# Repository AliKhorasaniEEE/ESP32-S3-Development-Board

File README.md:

# ESP32-S3 Development Board

A custom ESP32-S3-WROOM-1 development board designed in KiCad.

## Overview

This project is a two-layer ESP32-S3 development board featuring USB Type-C connectivity, USB-to-UART programming, onboard 3.3 V regulation, and access to all ESP32-S3 GPIO pins.

The board was designed as a learning project to gain practical experience in professional PCB design using KiCad.

---

## Features

- ESP32-S3-WROOM-1 module
- USB Type-C connector
- CP2102N USB-to-UART bridge
- AMS1117-3.3 V voltage regulator
- Reset and Boot buttons
- All 40 ESP32-S3 pins exposed
- Two-layer PCB
- Ground plane
- Decoupling capacitors placed according to the reference design

---

## Main Components

| Component | Part Number |
|-----------|-------------|
| MCU | ESP32-S3-WROOM-1 |
| USB-UART | CP2102N |
| Voltage Regulator | AMS1117-3.3 |
| USB Connector | USB Type-C 16-Pin |

---

## Software

Designed using:

- KiCad 10.0.4

---

## Repository Structure

Hardware/
KiCad project files

Images/
PCB renders and screenshots

---

## Images

### PCB

### Schematic

### 3D View

---

## Project Status

Current Revision: A

Prototype

**Hardware has not yet been manufactured or electrically validated.**

---

## Future Improvements

- Replace AMS1117 with a low-dropout regulator
- Improve ground stitching
- Optimize routing
- Hardware validation
- Revision B

---
## References

- Espressif ESP32-S3 Hardware Design Guidelines
- Espressif ESP32-S3-WROOM-1 Datasheet
- CP2102N Datasheet
- KiCad Official Libraries

## License

MIT License

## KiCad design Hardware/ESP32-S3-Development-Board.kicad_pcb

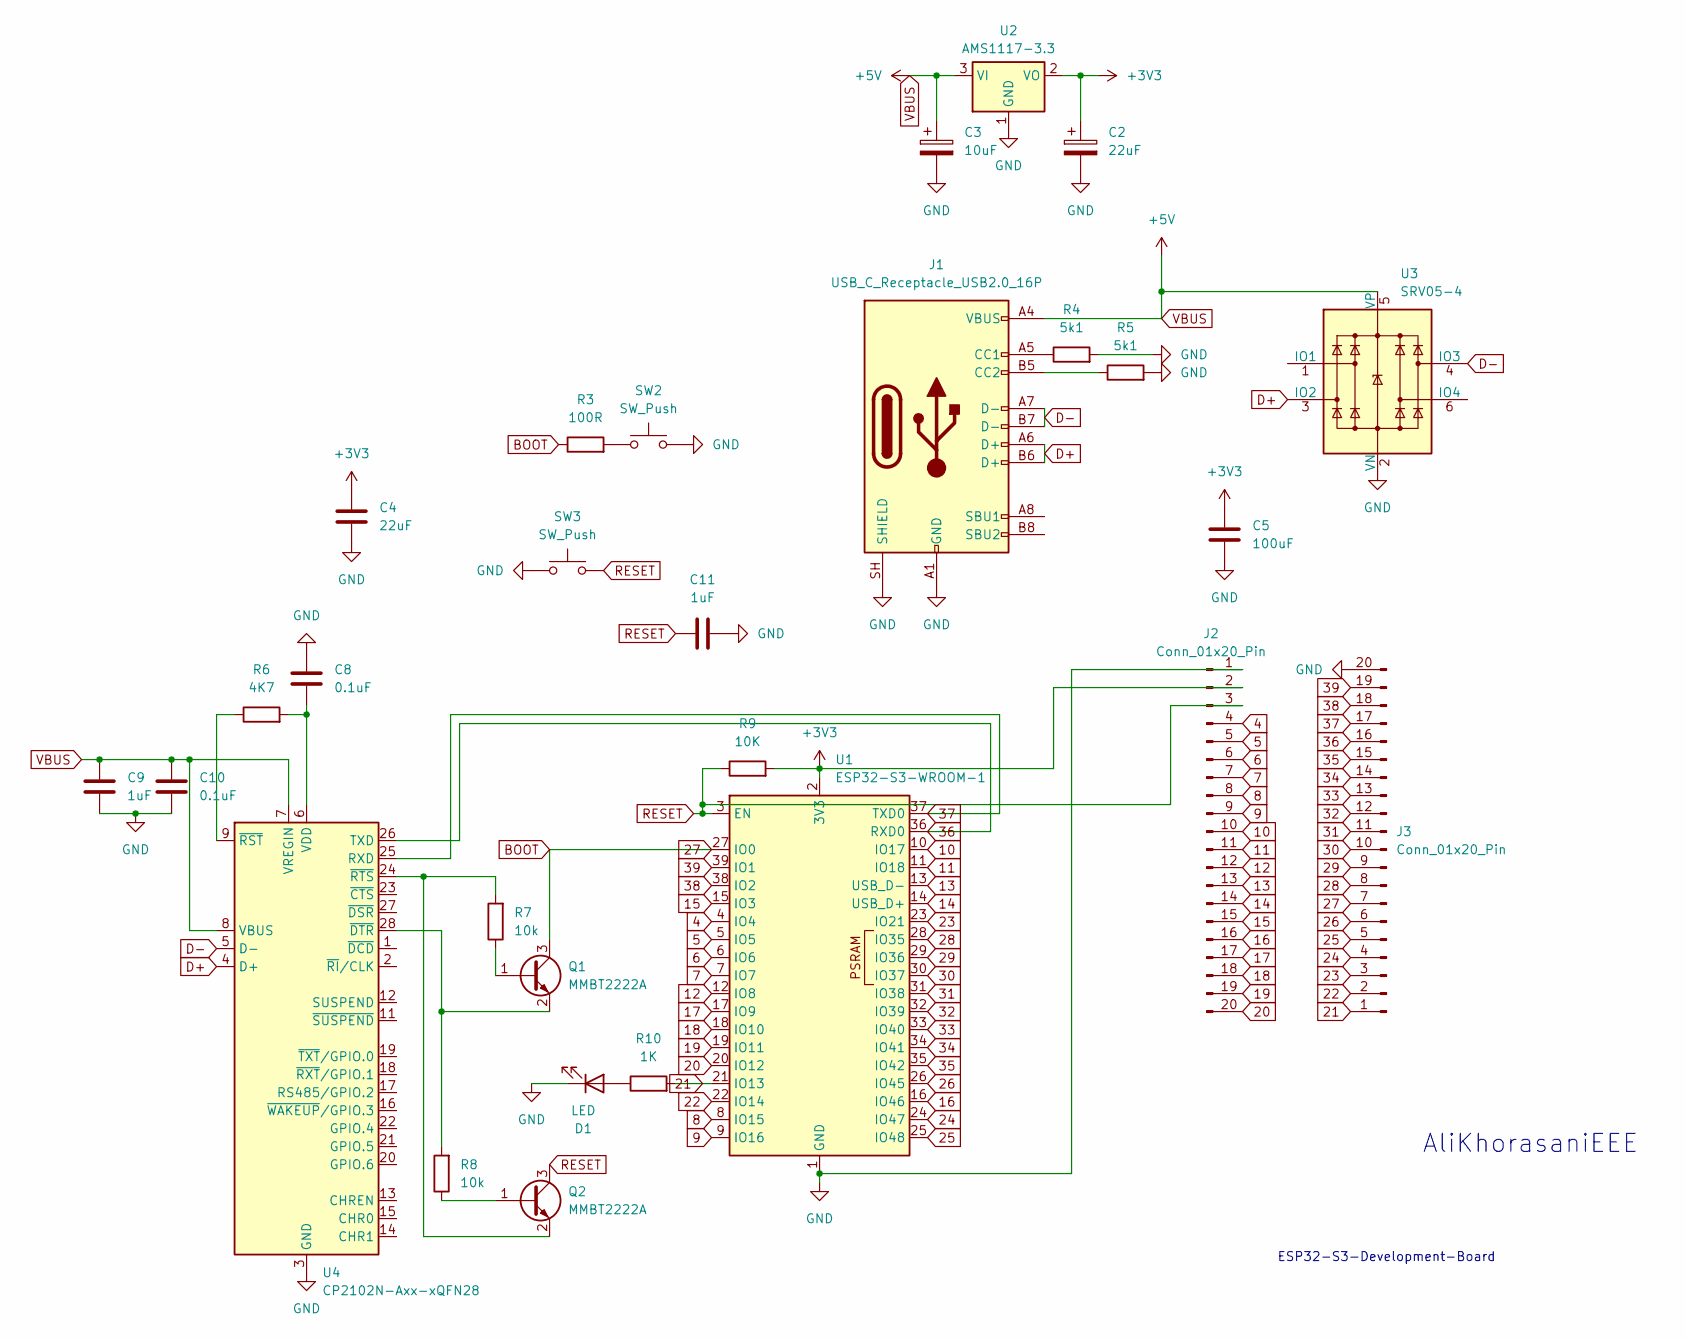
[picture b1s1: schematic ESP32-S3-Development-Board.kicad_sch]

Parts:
C2, C4: 22uF; C_1206_3216Metric
C3: 10uF; C_1206_3216Metric
C5: 100uF; C_1206_3216Metric
C8, C10: 0.1uF; C_1206_3216Metric
C9, C11: 1uF; C_1206_3216Metric
D1: LED; LED_0603_1608Metric
J1: USB_C_Receptacle_USB2.0_16P; USB_C_Receptacle_GCT_USB4105-xx-A_16P_TopMnt_Horizontal
J2, J3: Conn_01x20_Pin; PinHeader_1x20_P1.00mm_Vertical
Q1, Q2: MMBT2222A; SOT-23
R3: 100R; R_0805_2012Metric
R4, R5: 5k1; R_0805_2012Metric
R6: 4K7; R_0805_2012Metric
R7, R8: 10k; R_0805_2012Metric
R9: 10K; R_0805_2012Metric
R10: 1K; R_0805_2012Metric
SW2, SW3: SW_Push; SW_Push_SPST_NO_Alps_SKRK
U1: ESP32-S3-WROOM-1
U2: AMS1117-3.3; SOT-223-3_TabPin2
U3: SRV05-4; SOT-23-6
U4: CP2102N-Axx-xQFN28; QFN-28-1EP_5x5mm_P0.5mm_EP3.35x3.35mm

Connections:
4: J2.4, U1.4 (IO4)
5: J2.5, U1.5 (IO5)
6: J2.6, U1.6 (IO6)
7: J2.7, U1.7 (IO7)
8: J2.8, U1.8 (IO15)
9: J2.9, U1.9 (IO16)
10: J2.10, U1.10 (IO17)
11: J2.11, U1.11 (IO18)
12: J2.12, U1.12 (IO8)
13: J2.13, U1.13 (USB_D-)
14: J2.14, U1.14 (USB_D+)
15: J2.15, U1.15 (IO3)
16: J2.16, U1.16 (IO46)
17: J2.17, U1.17 (IO9)
18: J2.18, U1.18 (IO10)
19: J2.19, U1.19 (IO11)
20: J2.20, U1.20 (IO12)
21: J3.1, R10.2, U1.21 (IO13)
22: J3.2, U1.22 (IO14)
23: J3.3, U1.23 (IO21)
24: J3.4, U1.24 (IO47)
25: J3.5, U1.25 (IO48)
26: J3.6, U1.26 (IO45)
27: J3.7, Q1.3 (C), R3.1, U1.27 (IO0)
28: J3.8, U1.28 (IO35)
29: J3.9, U1.29 (IO36)
30: J3.10, U1.30 (IO37)
31: J3.11, U1.31 (IO38)
32: J3.12, U1.32 (IO39)
33: J3.13, U1.33 (IO40)
34: J3.14, U1.34 (IO41)
35: J3.15, U1.35 (IO42)
36: J3.16, U1.36 (RXD0), U4.26 (TXD)
37: J3.17, U1.37 (TXD0), U4.25 (RXD)
38: J3.18, U1.38 (IO2)
39: J3.19, U1.39 (IO1)
+3V3: C2.1, C4.1, C5.1, J2.2, R9.2, U1.2 (3V3), U2.2 (VO)
D+: J1.A6 (D+), J1.B6 (D+), U3.3 (IO2), U4.4 (D+)
D-: J1.A7 (D-), J1.B7 (D-), U3.4 (IO3), U4.5 (D-)
GND: C2.2, C3.2, C4.2, C5.2, C8.2, C9.2, C10.1, C11.2, D1.1 (K), J1.A1 (GND), J1.A12 (GND), J1.B1 (GND), J1.B12 (GND), J1.SH (SHIELD), J2.1, J3.20, R4.2, R5.2, SW2.2, SW3.1, U1.1 (GND), U1.40 (GND), U1.41 (GND), U2.1 (GND), U3.2 (VN), U4.3 (GND), U4.29 (GND)
unnamed: D1.2 (A), R10.1
unnamed: J1.A5 (CC1), R4.1
unnamed: J1.B5 (CC2), R5.1
unnamed: Q1.1 (B), R7.1
unnamed: Q1.2 (E), R8.2, U4.28 (~DTR)
unnamed: Q2.1 (B), R8.1
unnamed: Q2.2 (E), R7.2, U4.24 (~RTS)
unnamed: R3.2, SW2.1
unnamed: C8.1, R6.2, U4.6 (VDD)
unnamed: R6.1, U4.9 (~RST)
RESET: C11.1, J2.3, Q2.3 (C), R9.1, SW3.2, U1.3 (EN)
VBUS: C3.1, C9.1, C10.2, J1.A4 (VBUS), J1.A9 (VBUS), J1.B4 (VBUS), J1.B9 (VBUS), U2.3 (VI), U3.5 (VP), U4.7 (VREGIN), U4.8 (VBUS)

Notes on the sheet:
AliKhorasaniEEE
ESP32-S3-Development-Board

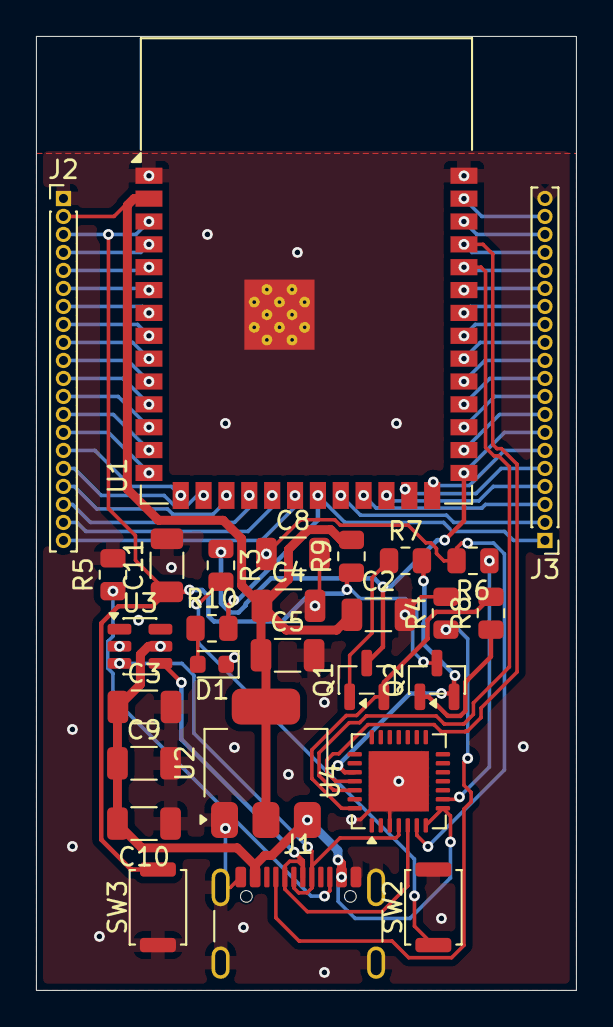
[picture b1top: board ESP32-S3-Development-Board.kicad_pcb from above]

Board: 2 copper layers, 30.0 x 53.0 mm, 28 parts (0 on the bottom side), 52 nets.
